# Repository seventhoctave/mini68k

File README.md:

# mini68k

`mini68k` is a small 68008 single-board computer based on the design at
http://www.christle.us/index.php?P=4.

The repository now includes both the board BIOS and a usable emulator for the
current hardware revisions. The emulator is aimed at BIOS bring-up and console
use, not cycle-exact emulation.

## Current status

- BIOS source and ROM build flow live under [bios/](bios/README.md)
- A Rust-based emulator lives under [emulator/](emulator/README.md)
- `v1` support covers the serial-console hardware: 68008-compatible CPU
  behavior, ROM, RAM, and SCC68681 DUART channel A
- `v2` support adds one video processor, either a Yamaha V9938 or a TI
  TMS9918A, each with a BIOS driver: a scrolling text console, bitmap drawing
  and sprites through the same `TRAP #0` API, and a `G` graphics demo in the
  monitor. The emulator models each chip's screen modes, sprites, timing and
  interrupts, plus the V9938's command engine.
- v2 hardware is a 100x100 system board with a VDP bus on its bottom edge,
  plus two plug-in VDP boards (V9938 or TMS9918A, one fitted at a time); see
  [hw/mini68k-v2/NOTES.md](hw/mini68k-v2/NOTES.md)

## Quick start

The supported development path is the Docker-based toolchain in this repo:

```sh
docker compose build dev
make bios-docker
make emu-build
make emu-test
make emu-run
```

`make emu-run` builds `bios/bios.bin` inside the container and starts the
emulator against it. A successful boot reaches the BIOS serial prompt:

```text
Mini 68008 BIOS
>
```

For the v2 video path, build the V9938-enabled ROM and run the emulator in
`v2` mode. Type `G` at the prompt for the graphics demo and `T` to return to
text:

```sh
make bios-docker V9938=1
make emu-run V9938=1 EMU_ARGS="--machine v2 --video window"

make bios-docker TMS9918=1
make emu-run TMS9918=1 EMU_ARGS="--machine v2 --vdp tms9918a --video window"
```

When `EMU_ARGS` includes `--video window`, `make emu-run` builds the BIOS in
Docker but runs the emulator on the host so it can open a desktop window.

To see the video BIOS in action, `make demo-run` builds the bouncing-ball demo
in [demos/](demos/) and opens the emulator with it running (add `TMS9918=1`
for the TMS9918A):

```sh
make demo-run
make demo-run TMS9918=1
```

## BIOS

Build the BIOS locally if you already have a 68k cross assembler and linker:

```sh
make -C bios
```

For emulator use, build a raw binary ROM image instead of the default S-record
output. Add `V9938=1` or `TMS9918=1` (not both) for the v2 video BIOS:

```sh
make -C bios FORMAT=binary
make -C bios FORMAT=binary V9938=1
make -C bios FORMAT=binary TMS9918=1
```

See [bios/README.md](bios/README.md) for BIOS-specific build and ROM programming
details, including the `TRAP #0` video API.

## Emulator

The emulator models two board profiles:

- `v1`: Musashi-backed CPU, ROM, RAM, and DUART console
- `v2`: the same base machine plus one VDP (`--vdp v9938|tms9918a`), with
  its screen modes, sprites, video timing, and host window rendering

The v1 GAL only decodes `A16:A15`, so the memory map aliases across the 20-bit
address space like the real hardware. The v2 path additionally qualifies `A14`
inside the `11` region so the DUART and VDP can coexist at their short-address
aliases.

See [emulator/README.md](emulator/README.md) for implementation details and
current limitations.

## Docker development environment

The repository includes a containerized cross-development environment in
[docker/](docker/) and [docker-compose.yml](docker-compose.yml). It provides:

- Rust 1.85 with `rustfmt`
- `m68k-unknown-elf-as` and `m68k-unknown-elf-ld` compatibility symlinks
- GNU m68k cross-binutils and cross-GCC packages

Useful top-level targets:

- `make bios-docker`: build `bios/bios.bin` in the container; pass `V9938=1`
  or `TMS9918=1` for a v2 ROM
- `make emu-build`: build the emulator in release mode
- `make emu-test`: run the emulator unit and integration tests
- `make emu-run`: boot the BIOS in the emulator; pass `EMU_ARGS` through to the
  CLI
- `make dev-shell`: open a shell inside the dev container

The checked-in `crosstool-ng.sparseimage` remains available as an optional local
workaround, but it is no longer the primary documented workflow.

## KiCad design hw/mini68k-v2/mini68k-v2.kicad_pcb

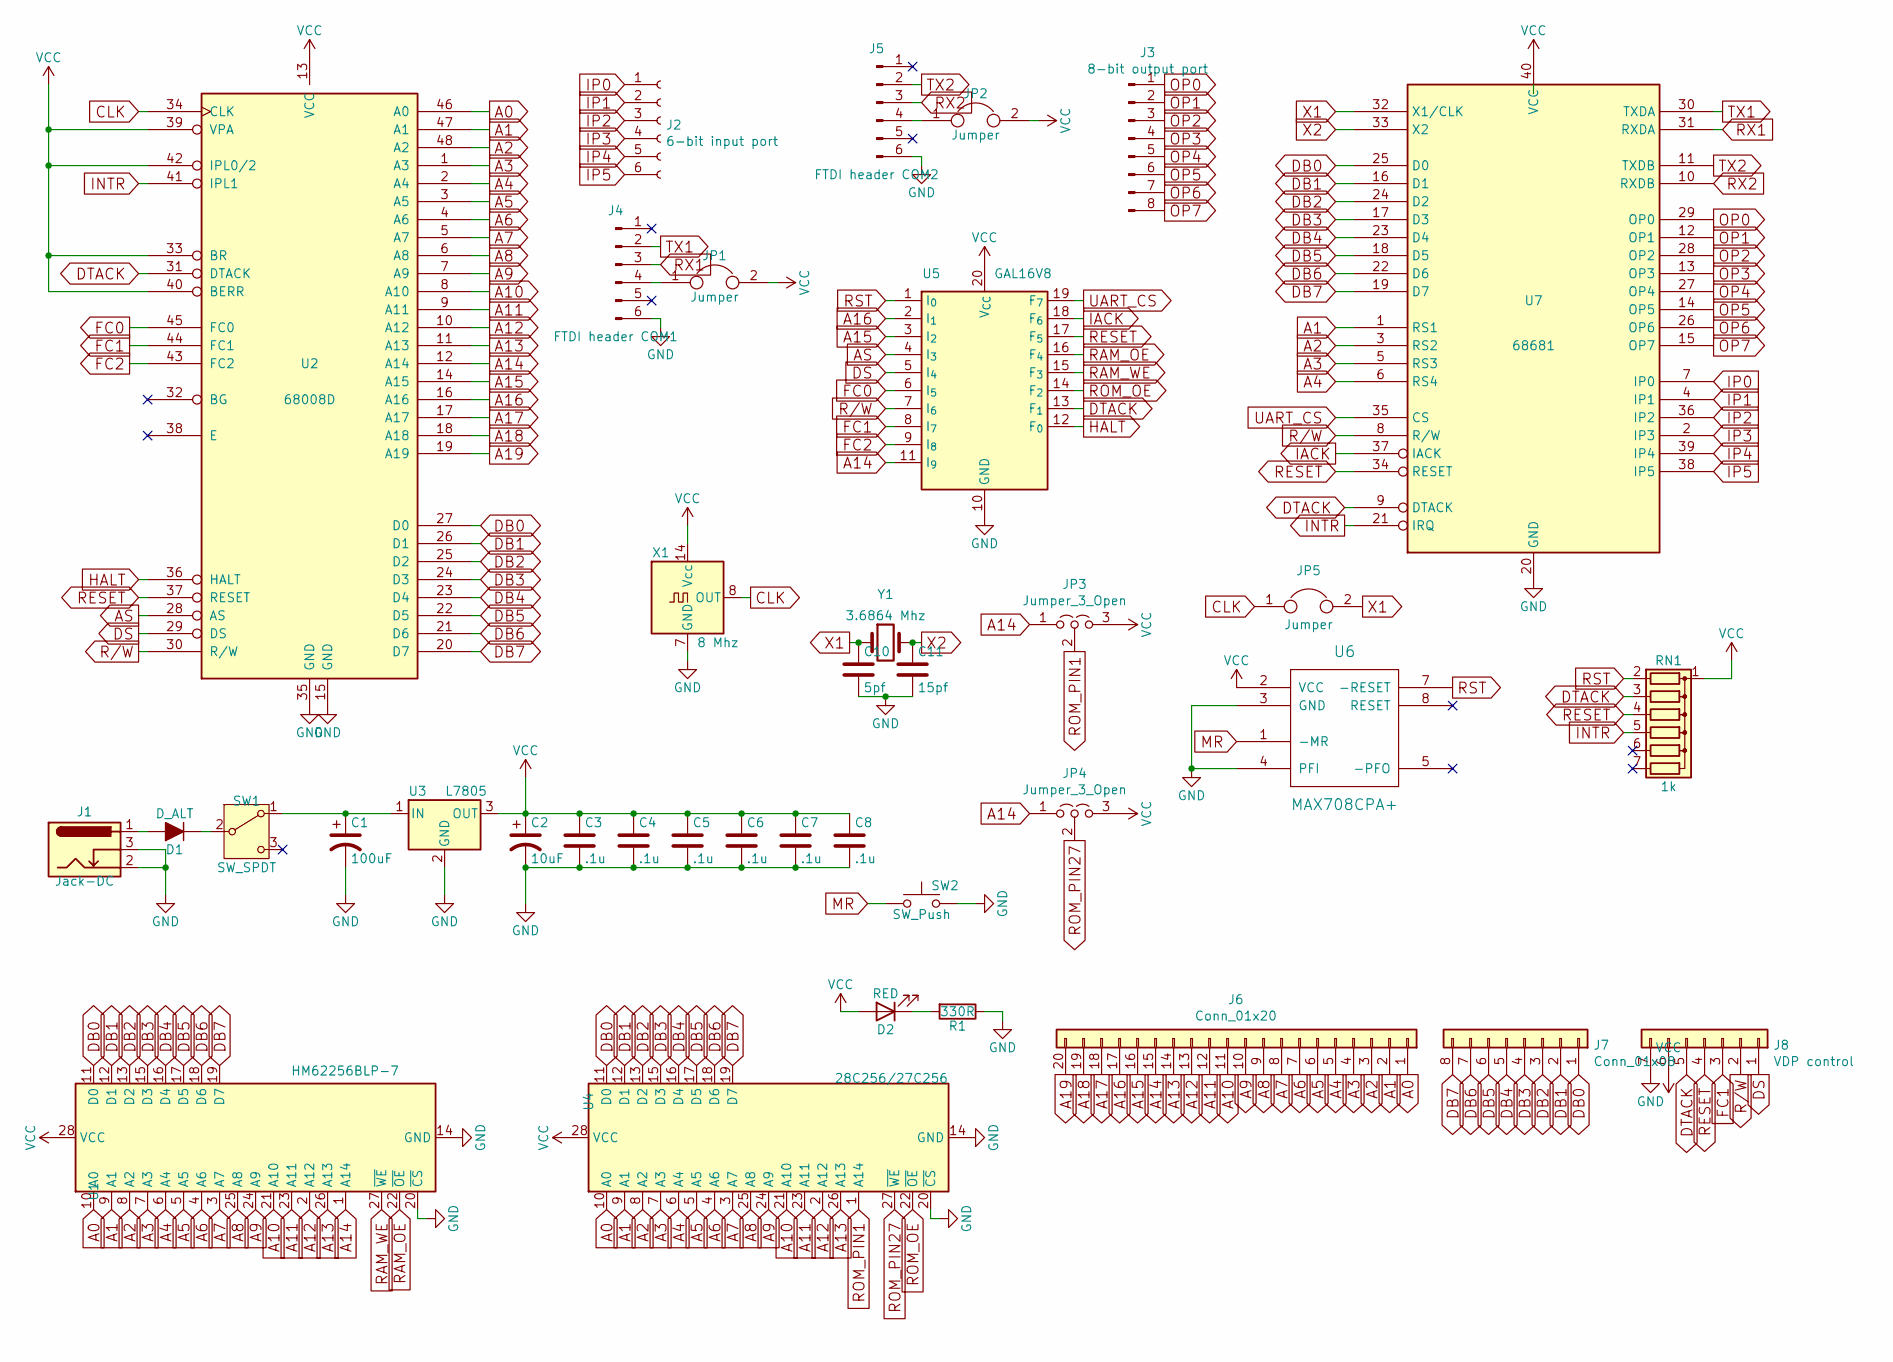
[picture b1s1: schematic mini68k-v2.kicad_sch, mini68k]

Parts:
C1: 100uF; CP_Radial_D5.0mm_P2.50mm
C2: 10uF; CP_Radial_D5.0mm_P2.50mm
C3, C4, C5, C6, C7, C8: .1u; C_Disc_D5.0mm_W2.5mm_P2.50mm
C10: 5pf; C_Disc_D5.0mm_W2.5mm_P2.50mm
C11: 15pf; C_Disc_D5.0mm_W2.5mm_P2.50mm
D1: D_ALT; D_DO-35_SOD27_P10.16mm_Horizontal
D2: RED; LED_D4.0mm
J1: Jack-DC; BarrelJack_Horizontal
J2: 6-bit input port; PinHeader_1x06_P2.54mm_Horizontal
J3: 8-bit output port; PinHeader_1x08_P2.54mm_Horizontal
J4: FTDI header COM1; PinHeader_1x06_P2.54mm_Horizontal
J5: FTDI header COM2; PinHeader_1x06_P2.54mm_Horizontal
J6: Conn_01x20; PinHeader_1x20_P2.54mm_Horizontal
J7: Conn_01x08; PinHeader_1x08_P2.54mm_Horizontal
J8: VDP control; PinHeader_1x07_P2.54mm_Horizontal
JP1, JP2: Jumper; PinHeader_1x02_P2.54mm_Vertical
JP3, JP4: Jumper_3_Open; PinHeader_1x03_P2.54mm_Vertical
JP5: Jumper; PinSocket_1x02_P2.54mm_Vertical
R1: 330R; R_Axial_DIN0207_L6.3mm_D2.5mm_P7.62mm_Horizontal
RN1: 1k; R_Array_SIP7
SW1: SW_SPDT; SW_E-Switch_EG1271_DPDT
SW2: SW_Push; SW_PUSH_6mm
U1: HM62256BLP-7; DIP-28_W15.24mm_LongPads
U2: 68008D; DIP-48_W15.24mm_LongPads
U3: L7805; TO-220-3_Horizontal_TabDown
U4: 28C256/27C256; DIP-28_W15.24mm_LongPads
U5: GAL16V8; DIP-20_W7.62mm_LongPads
U6: MAX708CPA+; DIP-8_W7.62mm_LongPads
U7: 68681; DIP-40_W15.24mm_LongPads
X1: 8 Mhz; Oscillator_DIP-14_LargePads
Y1: 3.6864 Mhz; Crystal_HC49-4H_Vertical

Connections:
A0: J6.1, U1.10 (A0), U2.46 (A0), U4.10 (A0)
A1: J6.2, U1.9 (A1), U2.47 (A1), U4.9 (A1), U7.1 (RS1)
A2: J6.3, U1.8 (A2), U2.48 (A2), U4.8 (A2), U7.3 (RS2)
A3: J6.4, U1.7 (A3), U2.1 (A3), U4.7 (A3), U7.5 (RS3)
A4: J6.5, U1.6 (A4), U2.2 (A4), U4.6 (A4), U7.6 (RS4)
A5: J6.6, U1.5 (A5), U2.3 (A5), U4.5 (A5)
A6: J6.7, U1.4 (A6), U2.4 (A6), U4.4 (A6)
A7: J6.8, U1.3 (A7), U2.5 (A7), U4.3 (A7)
A8: J6.9, U1.25 (A8), U2.6 (A8), U4.25 (A8)
A9: J6.10, U1.24 (A9), U2.7 (A9), U4.24 (A9)
A10: J6.11, U1.21 (A10), U2.8 (A10), U4.21 (A10)
A11: J6.12, U1.23 (A11), U2.9 (A11), U4.23 (A11)
A12: J6.13, U1.2 (A12), U2.10 (A12), U4.2 (A12)
A13: J6.14, U1.26 (A13), U2.11 (A13), U4.26 (A13)
A14: J6.15, JP3.1 (A), JP4.1 (A), U1.1 (A14), U2.12 (A14), U5.11 (I_{9})
A15: J6.16, U2.14 (A15), U5.3 (I_{2})
A16: J6.17, U2.16 (A16), U5.2 (I_{1})
A17: J6.18, U2.17 (A17)
A18: J6.19, U2.18 (A18)
A19: J6.20, U2.19 (A19)
AS: U2.28 (AS), U5.4 (I_{3})
CLK: JP5.1, U2.34 (CLK), X1.8 (OUT)
DB0: J7.1, U1.11 (D0), U2.27 (D0), U4.11 (D0), U7.25 (D0)
DB1: J7.2, U1.12 (D1), U2.26 (D1), U4.12 (D1), U7.16 (D1)
DB2: J7.3, U1.13 (D2), U2.25 (D2), U4.13 (D2), U7.24 (D2)
DB3: J7.4, U1.15 (D3), U2.24 (D3), U4.15 (D3), U7.17 (D3)
DB4: J7.5, U1.16 (D4), U2.23 (D4), U4.16 (D4), U7.23 (D4)
DB5: J7.6, U1.17 (D5), U2.22 (D5), U4.17 (D5), U7.18 (D5)
DB6: J7.7, U1.18 (D6), U2.21 (D6), U4.18 (D6), U7.22 (D6)
DB7: J7.8, U1.19 (D7), U2.20 (D7), U4.19 (D7), U7.19 (D7)
DS: J8.1, U2.29 (DS), U5.5 (I_{4})
DTACK: J8.5, RN1.3 (R2), U2.31 (DTACK), U5.13 (F_{1}), U7.9 (DTACK)
FC0: U2.45 (FC0), U5.6 (I_{5})
FC1: J8.3, U2.44 (FC1), U5.8 (I_{7})
FC2: U2.43 (FC2), U5.9 (I_{8})
GND: C1.2, C2.2, C3.2, C4.2, C5.2, C6.2, C7.2, C8.2, C10.2, C11.2, J1.2, J1.3, J4.6, J5.6, J8.7, R1.1, SW2.2, U1.14 (GND), U1.20 (~CS), U2.15 (GND), U2.35 (GND), U3.2 (GND), U4.14 (GND), U4.20 (~CS), U5.10 (GND), U6.3 (GND), U6.4 (PFI), U7.20 (GND), X1.7 (GND)
HALT: U2.36 (HALT), U5.12 (F_{0})
IACK: U5.18 (F_{6}), U7.37 (IACK)
INTR: RN1.5 (R4), U2.41 (IPL1), U7.21 (IRQ)
IP0: J2.1, U7.7 (IP0)
IP1: J2.2, U7.4 (IP1)
IP2: J2.3, U7.36 (IP2)
IP3: J2.4, U7.2 (IP3)
IP4: J2.5, U7.39 (IP4)
IP5: J2.6, U7.38 (IP5)
MR: SW2.1, U6.1 (-MR)
unnamed: D1.2 (A), J1.1
unnamed: D1.1 (K), SW1.2 (B)
unnamed: D2.1 (K), R1.2
unnamed: J4.4, JP1.1
unnamed: J5.4, JP2.1
unnamed: C1.1, SW1.1 (A), U3.1 (IN)
OP0: J3.1, U7.29 (OP0)
OP1: J3.2, U7.12 (OP1)
OP2: J3.3, U7.28 (OP2)
OP3: J3.4, U7.13 (OP3)
OP4: J3.5, U7.27 (OP4)
OP5: J3.6, U7.14 (OP5)
OP6: J3.7, U7.26 (OP6)
OP7: J3.8, U7.15 (OP7)
RAM_OE: U1.22 (~OE), U5.16 (F_{4})
RAM_WE: U1.27 (~WE), U5.15 (F_{3})
RESET: J8.4, RN1.4 (R3), U2.37 (RESET), U5.17 (F_{5}), U7.34 (RESET)
ROM_OE: U4.22 (~OE), U5.14 (F_{2})
ROM_PIN1: JP3.2 (C), U4.1 (A14)
ROM_PIN27: JP4.2 (C), U4.27 (~WE)
RST: RN1.2 (R1), U5.1 (I_{0}), U6.7 (-RESET)
RX1: J4.3, U7.31 (RXDA)
RX2: J5.3, U7.10 (RXDB)
R/W: J8.2, U2.30 (R/W), U5.7 (I_{6}), U7.8 (R/W)
TX1: J4.2, U7.30 (TXDA)
TX2: J5.2, U7.11 (TXDB)
UART_CS: U5.19 (F_{7}), U7.35 (CS)
VCC: C2.1, C3.1, C4.1, C5.1, C6.1, C7.1, C8.1, D2.2 (A), J8.6, JP1.2, JP2.2, JP3.3 (B), JP4.3 (B), RN1.1 (common), U1.28 (VCC), U2.13 (VCC), U2.33 (BR), U2.39 (VPA), U2.40 (BERR), U2.42 (IPL0/2), U3.3 (OUT), U4.28 (VCC), U5.20 (V_{CC}), U6.2 (VCC), U7.40 (VCC), X1.14 (Vcc)
X1: C10.1, JP5.2, U7.32 (X1/CLK), Y1.1
X2: C11.1, U7.33 (X2), Y1.2

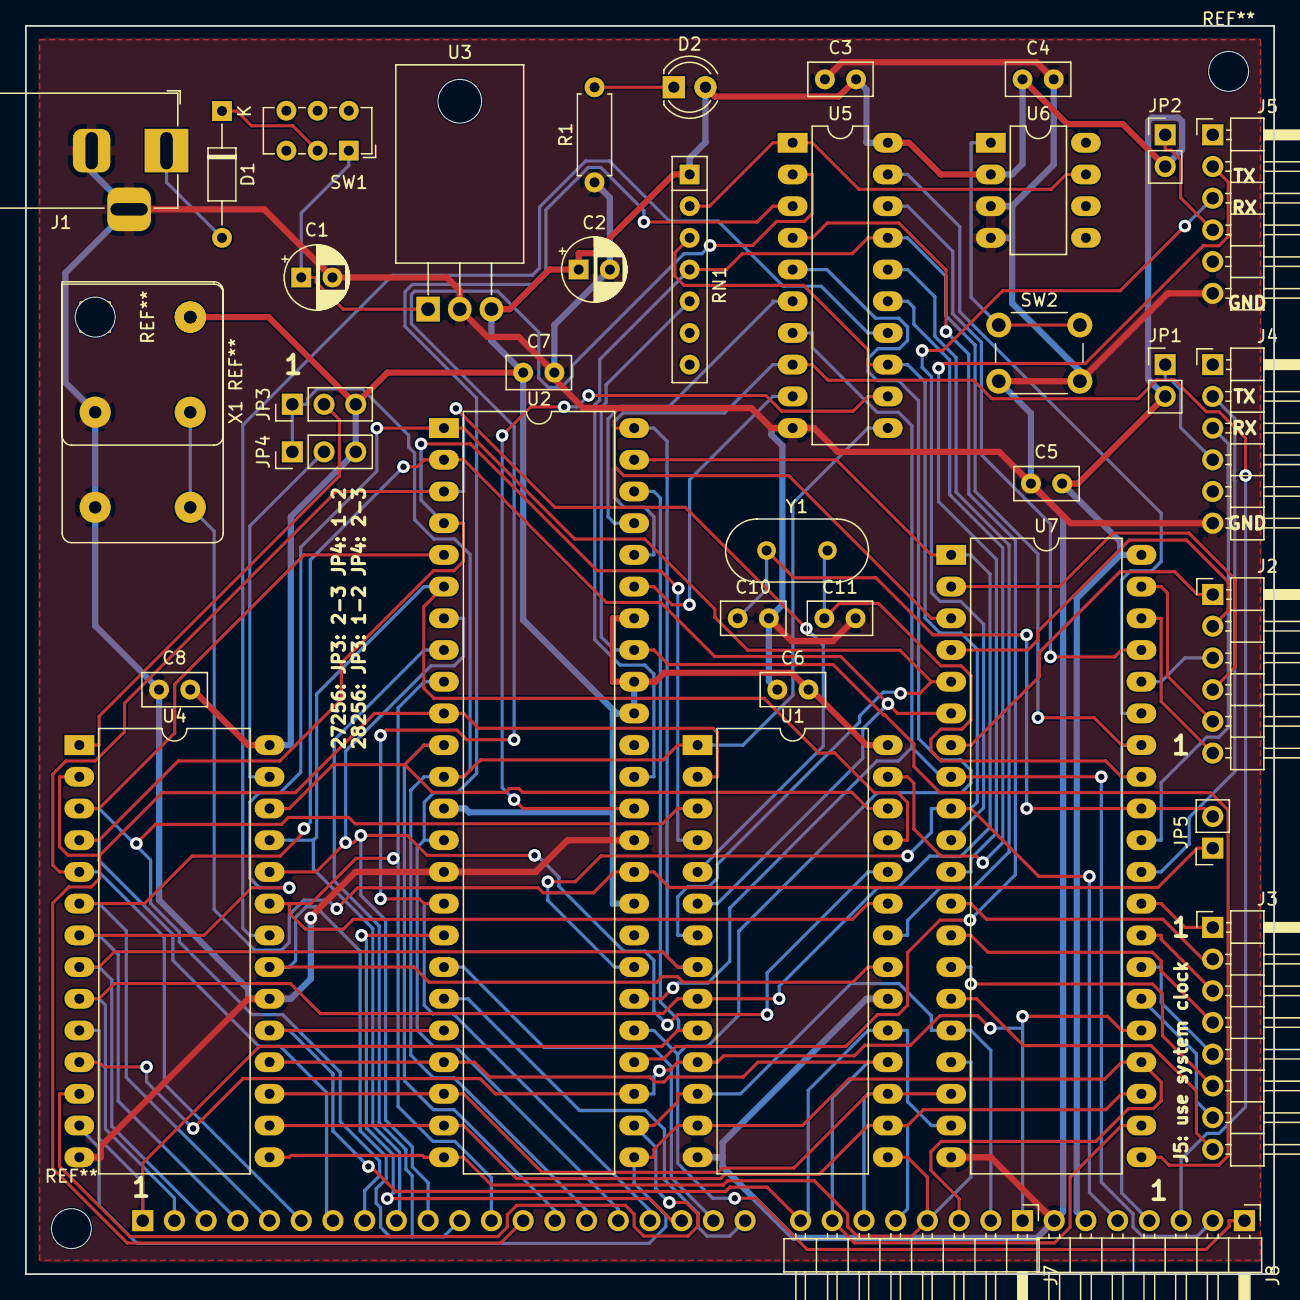
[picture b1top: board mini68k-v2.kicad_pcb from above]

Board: 2 copper layers, 100.0 x 100.0 mm, 38 parts (1 on the bottom side), 76 nets.

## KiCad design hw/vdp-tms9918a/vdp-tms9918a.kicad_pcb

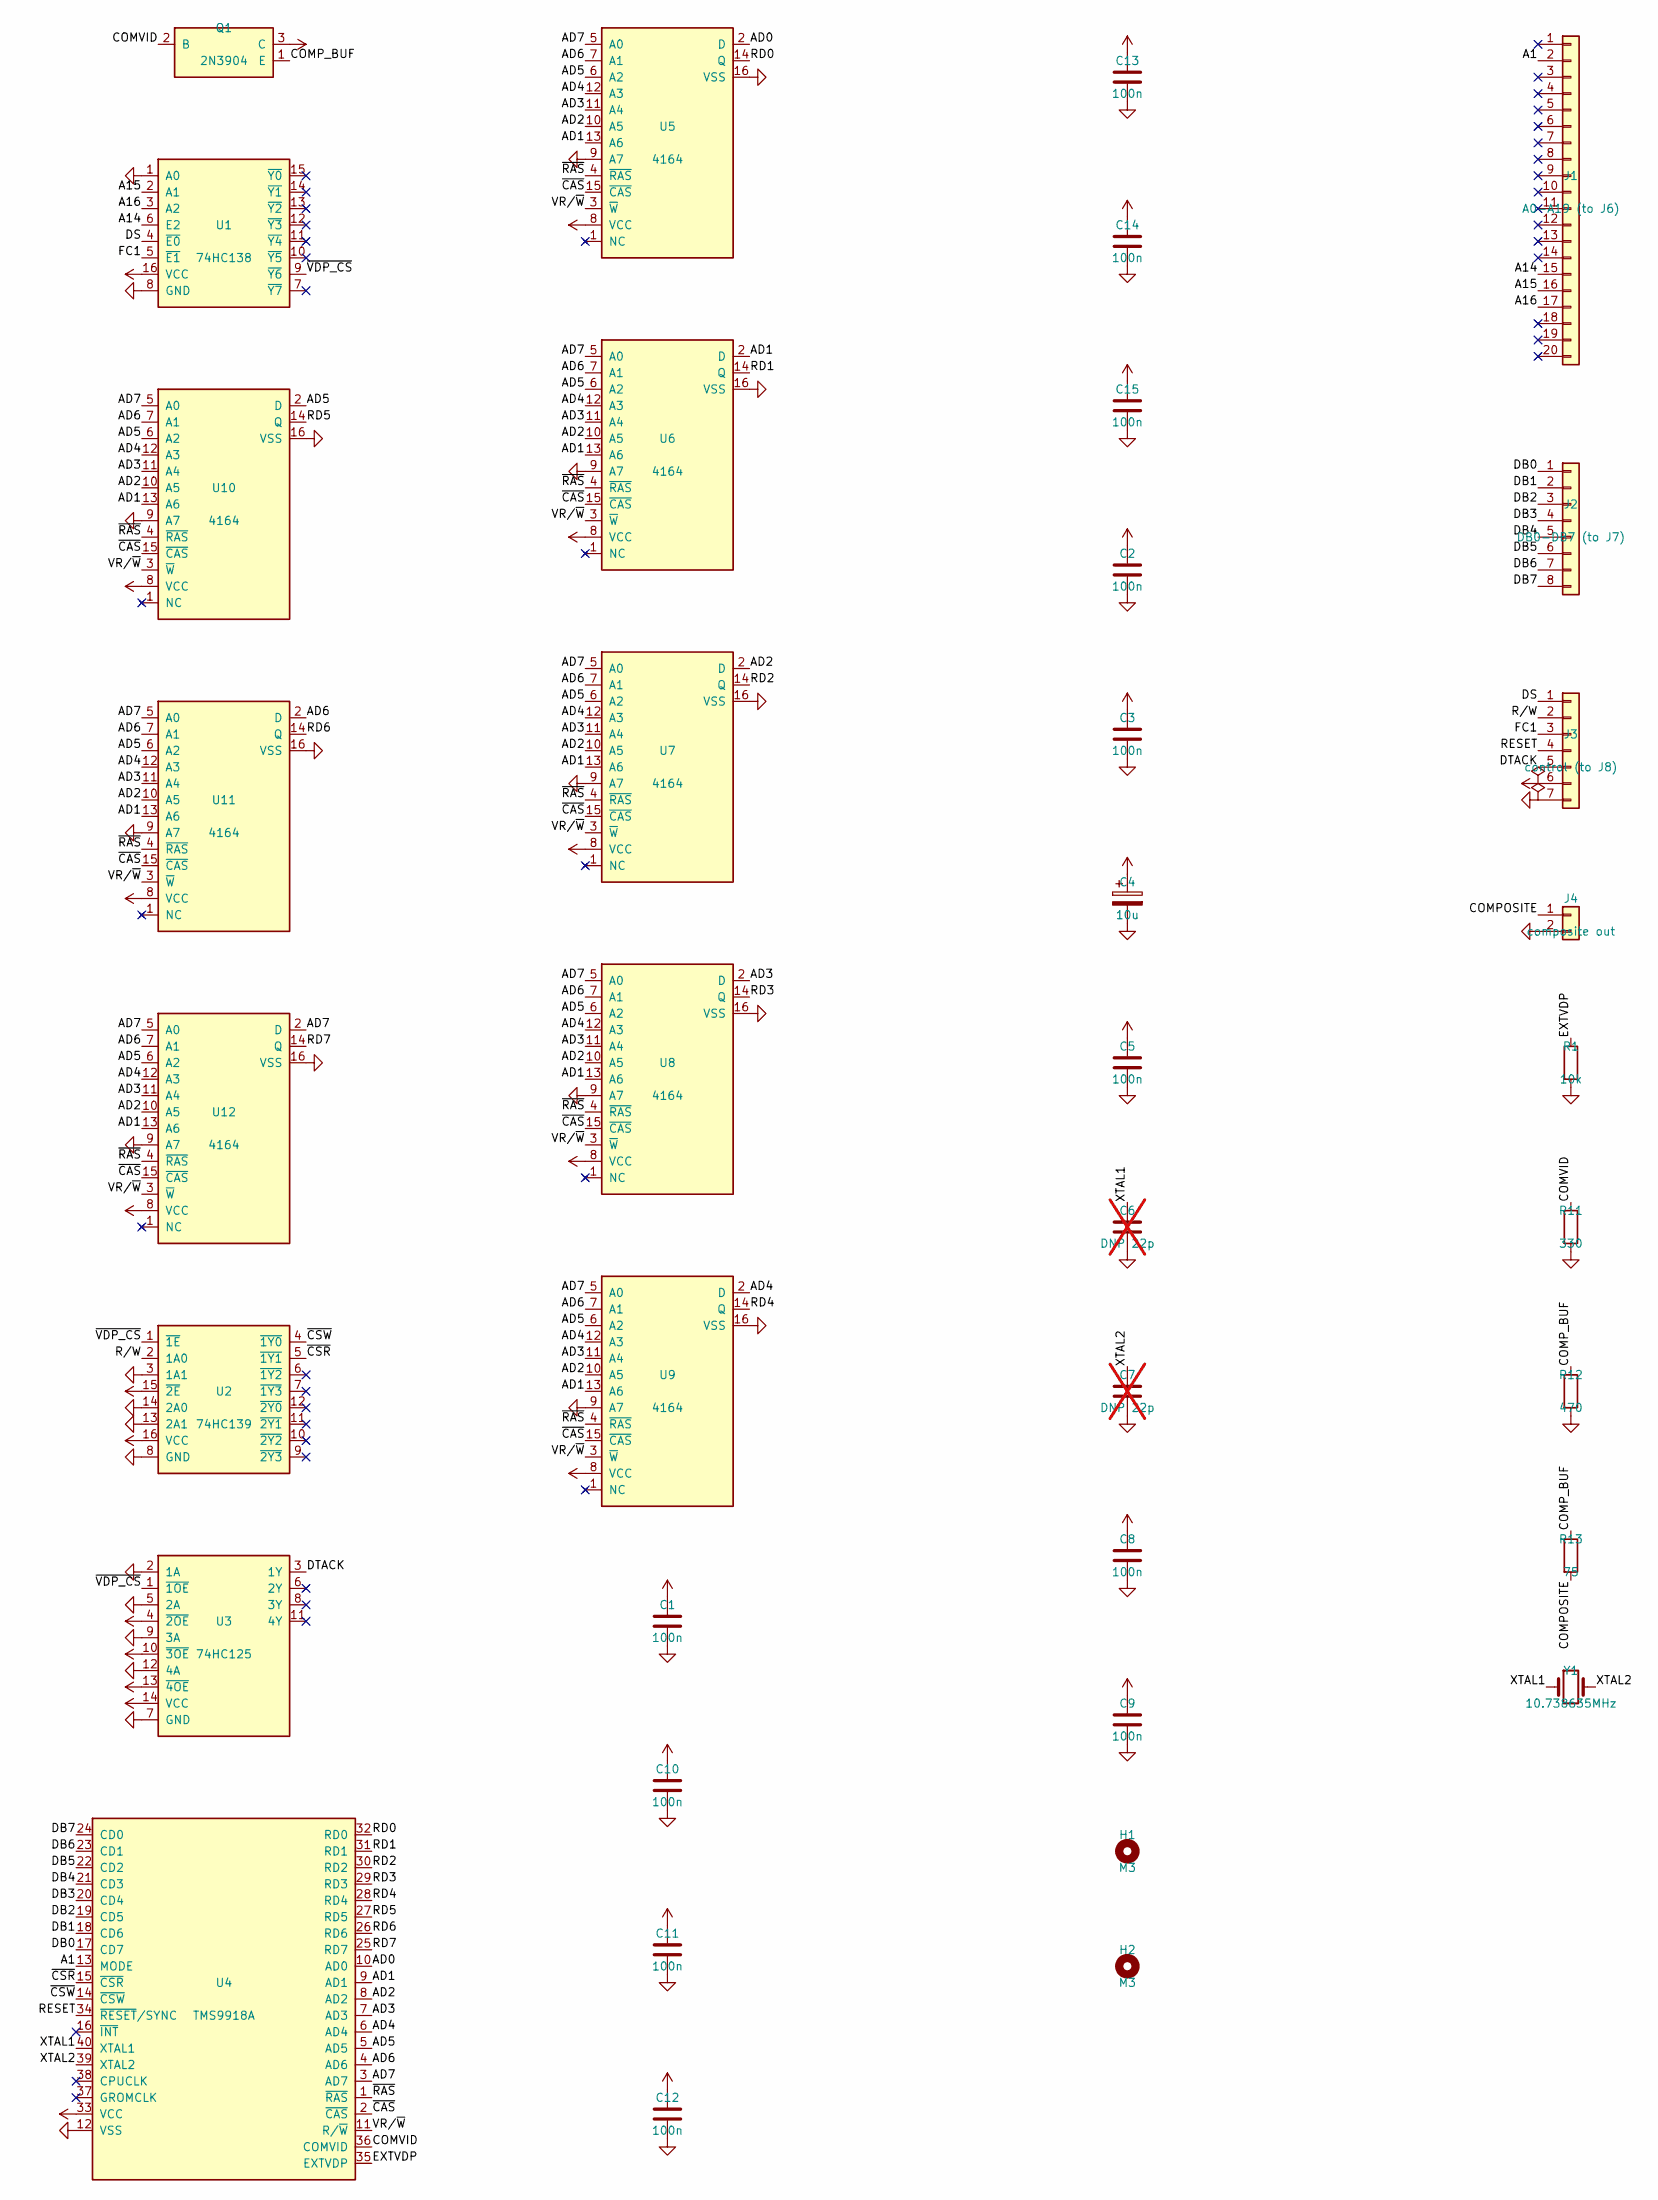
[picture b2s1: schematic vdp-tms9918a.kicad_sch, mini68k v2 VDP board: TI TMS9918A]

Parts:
C1, C2, C3, C5, C8, C9, C10, C11, C12, C13, C14, C15: 100n; C_Disc_D5.0mm_W2.5mm_P2.50mm
C4: 10u; CP_Radial_D5.0mm_P2.50mm
C6, C7: DNP 22p; C_Disc_D5.0mm_W2.5mm_P2.50mm; not fitted
H1, H2: M3; MountingHole_3.2mm_M3
J1: A0-A19 (to J6); PinSocket_1x20_P2.54mm_Horizontal
J2: DB0-DB7 (to J7); PinSocket_1x08_P2.54mm_Horizontal
J3: control (to J8); PinSocket_1x07_P2.54mm_Horizontal
J4: composite out; PinHeader_1x02_P2.54mm_Vertical
Q1: 2N3904; TO-92_Inline_Wide
R1: 10k; R_Axial_DIN0207_L6.3mm_D2.5mm_P7.62mm_Horizontal
R11: 330; R_Axial_DIN0207_L6.3mm_D2.5mm_P7.62mm_Horizontal
R12: 470; R_Axial_DIN0207_L6.3mm_D2.5mm_P7.62mm_Horizontal
R13: 75; R_Axial_DIN0207_L6.3mm_D2.5mm_P7.62mm_Horizontal
U1: 74HC138; DIP-16_W7.62mm_LongPads
U2: 74HC139; DIP-16_W7.62mm_LongPads
U3: 74HC125; DIP-14_W7.62mm_LongPads
U4: TMS9918A; DIP-40_W15.24mm_LongPads
U5, U6, U7, U8, U9, U10, U11, U12: 4164; DIP-16_W7.62mm_LongPads
Y1: 10.738635MHz; Crystal_HC49-4H_Vertical

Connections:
/A1: J1.2, U4.13 (MODE)
/A14: J1.15, U1.6 (E2)
/A15: J1.16, U1.2 (A1)
/A16: J1.17, U1.3 (A2)
/AD0: U4.10 (AD0), U5.2 (D)
/AD1: U4.9 (AD1), U5.13 (A6), U6.2 (D), U6.13 (A6), U7.13 (A6), U8.13 (A6), U9.13 (A6), U10.13 (A6), U11.13 (A6), U12.13 (A6)
/AD2: U4.8 (AD2), U5.10 (A5), U6.10 (A5), U7.2 (D), U7.10 (A5), U8.10 (A5), U9.10 (A5), U10.10 (A5), U11.10 (A5), U12.10 (A5)
/AD3: U4.7 (AD3), U5.11 (A4), U6.11 (A4), U7.11 (A4), U8.2 (D), U8.11 (A4), U9.11 (A4), U10.11 (A4), U11.11 (A4), U12.11 (A4)
/AD4: U4.6 (AD4), U5.12 (A3), U6.12 (A3), U7.12 (A3), U8.12 (A3), U9.2 (D), U9.12 (A3), U10.12 (A3), U11.12 (A3), U12.12 (A3)
/AD5: U4.5 (AD5), U5.6 (A2), U6.6 (A2), U7.6 (A2), U8.6 (A2), U9.6 (A2), U10.2 (D), U10.6 (A2), U11.6 (A2), U12.6 (A2)
/AD6: U4.4 (AD6), U5.7 (A1), U6.7 (A1), U7.7 (A1), U8.7 (A1), U9.7 (A1), U10.7 (A1), U11.2 (D), U11.7 (A1), U12.7 (A1)
/AD7: U4.3 (AD7), U5.5 (A0), U6.5 (A0), U7.5 (A0), U8.5 (A0), U9.5 (A0), U10.5 (A0), U11.5 (A0), U12.2 (D), U12.5 (A0)
/COMPOSITE: J4.1, R13.2
/COMP_BUF: Q1.1 (E), R12.1, R13.1
/COMVID: Q1.2 (B), R11.1, U4.36 (COMVID)
/DB0: J2.1, U4.17 (CD7)
/DB1: J2.2, U4.18 (CD6)
/DB2: J2.3, U4.19 (CD5)
/DB3: J2.4, U4.20 (CD4)
/DB4: J2.5, U4.21 (CD3)
/DB5: J2.6, U4.22 (CD2)
/DB6: J2.7, U4.23 (CD1)
/DB7: J2.8, U4.24 (CD0)
/DS: J3.1, U1.4 (~E0)
/DTACK: J3.5, U3.3 (1Y)
/EXTVDP: R1.1, U4.35 (EXTVDP)
/FC1: J3.3, U1.5 (~E1)
/RD0: U4.32 (RD0), U5.14 (Q)
/RD1: U4.31 (RD1), U6.14 (Q)
/RD2: U4.30 (RD2), U7.14 (Q)
/RD3: U4.29 (RD3), U8.14 (Q)
/RD4: U4.28 (RD4), U9.14 (Q)
/RD5: U4.27 (RD5), U10.14 (Q)
/RD6: U4.26 (RD6), U11.14 (Q)
/RD7: U4.25 (RD7), U12.14 (Q)
/RESET: J3.4, U4.34 (~RESET/SYNC)
/R/W: J3.2, U2.2 (1A0)
/VR/~W: U4.11 (R/~W), U5.3 (~W), U6.3 (~W), U7.3 (~W), U8.3 (~W), U9.3 (~W), U10.3 (~W), U11.3 (~W), U12.3 (~W)
/XTAL1: C6.1, U4.40 (XTAL1), Y1.1
/XTAL2: C7.1, U4.39 (XTAL2), Y1.2
/~CAS: U4.2 (~CAS), U5.15 (~CAS), U6.15 (~CAS), U7.15 (~CAS), U8.15 (~CAS), U9.15 (~CAS), U10.15 (~CAS), U11.15 (~CAS), U12.15 (~CAS)
/~CSR: U2.5 (~1Y1), U4.15 (~CSR)
/~CSW: U2.4 (~1Y0), U4.14 (~CSW)
/~RAS: U4.1 (~RAS), U5.4 (~RAS), U6.4 (~RAS), U7.4 (~RAS), U8.4 (~RAS), U9.4 (~RAS), U10.4 (~RAS), U11.4 (~RAS), U12.4 (~RAS)
/~VDP_CS: U1.9 (~Y6), U2.1 (~1E), U3.1 (~1OE)
GND: C1.2, C2.2, C3.2, C4.2, C5.2, C6.2, C7.2, C8.2, C9.2, C10.2, C11.2, C12.2, C13.2, C14.2, C15.2, J3.7, J4.2, R1.2, R11.2, R12.2, U1.1 (A0), U1.8 (GND), U2.3 (1A1), U2.8 (GND), U2.13 (2A1), U2.14 (2A0), U3.2 (1A), U3.5 (2A), U3.7 (GND), U3.9 (3A), U3.12 (4A), U4.12 (VSS), U5.9 (A7), U5.16 (VSS), U6.9 (A7), U6.16 (VSS), U7.9 (A7), U7.16 (VSS), U8.9 (A7), U8.16 (VSS), U9.9 (A7), U9.16 (VSS), U10.9 (A7), U10.16 (VSS), U11.9 (A7), U11.16 (VSS), U12.9 (A7), U12.16 (VSS)
VCC: C1.1, C2.1, C3.1, C4.1, C5.1, C8.1, C9.1, C10.1, C11.1, C12.1, C13.1, C14.1, C15.1, J3.6, Q1.3 (C), U1.16 (VCC), U2.15 (~2E), U2.16 (VCC), U3.4 (~2OE), U3.10 (~3OE), U3.13 (~4OE), U3.14 (VCC), U4.33 (VCC), U5.8 (VCC), U6.8 (VCC), U7.8 (VCC), U8.8 (VCC), U9.8 (VCC), U10.8 (VCC), U11.8 (VCC), U12.8 (VCC)

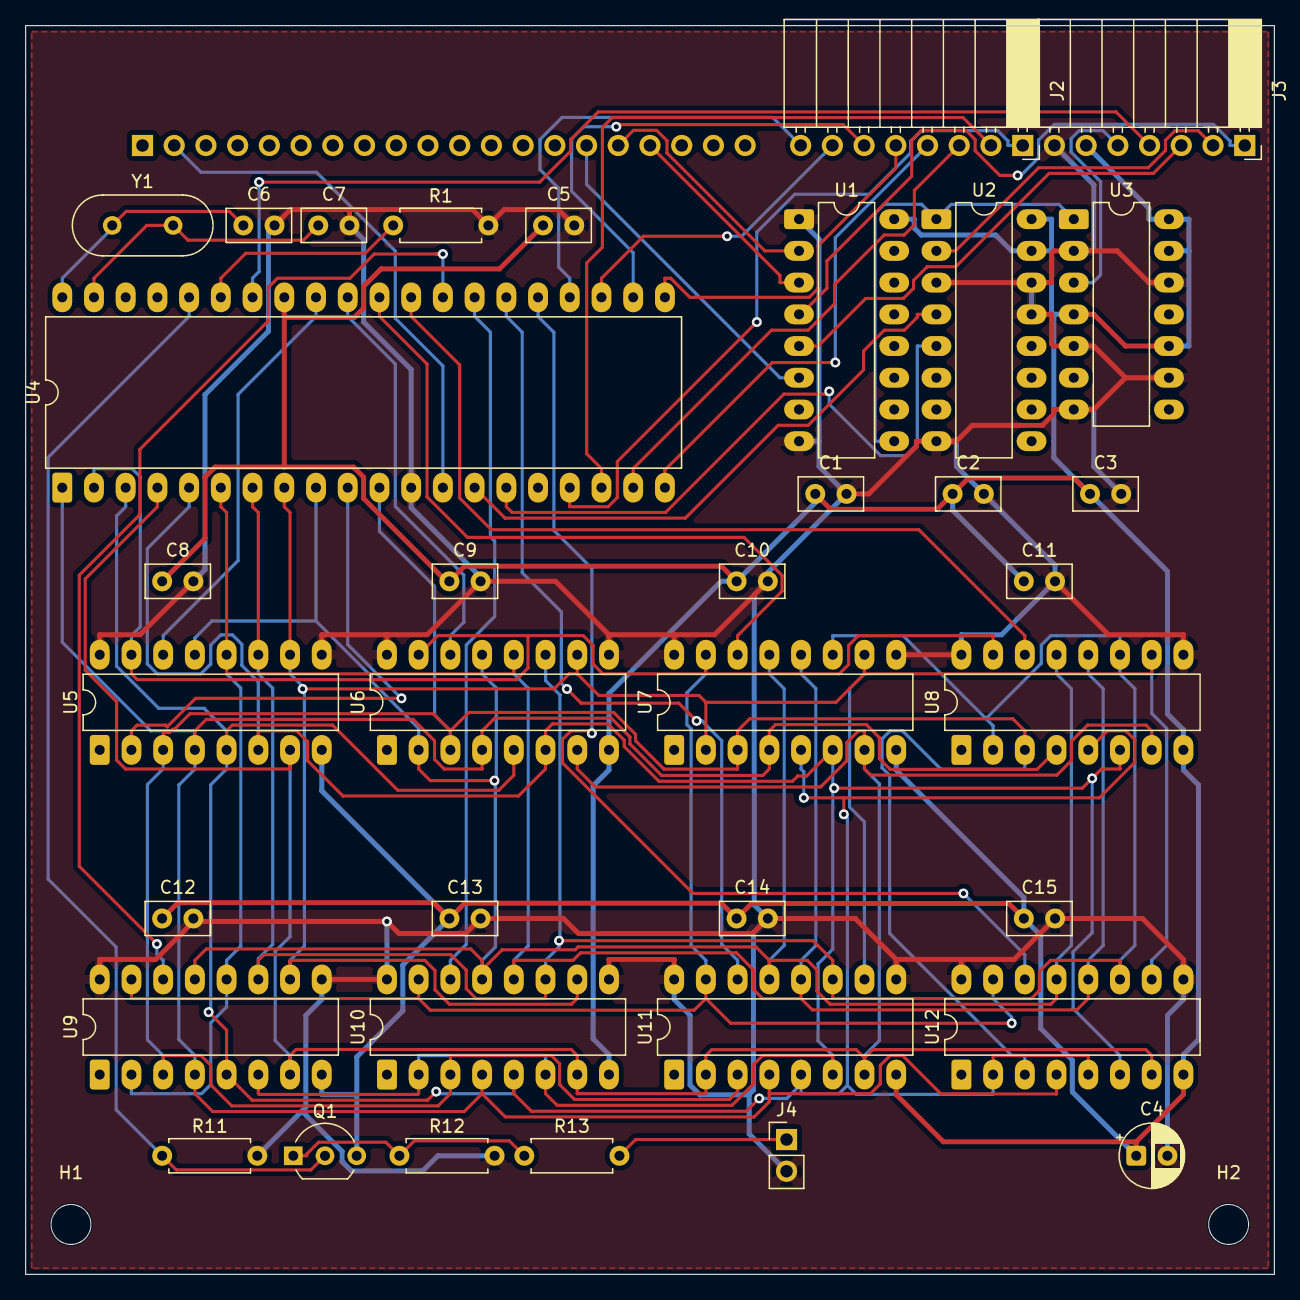
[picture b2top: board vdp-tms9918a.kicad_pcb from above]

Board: 2 copper layers, 100.0 x 100.0 mm, 39 parts (1 on the bottom side), 47 nets.
